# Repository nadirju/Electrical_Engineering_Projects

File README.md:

# Electrical_Engineering_Projects
This repository contains the projects I have done related to Electrical Engineering.

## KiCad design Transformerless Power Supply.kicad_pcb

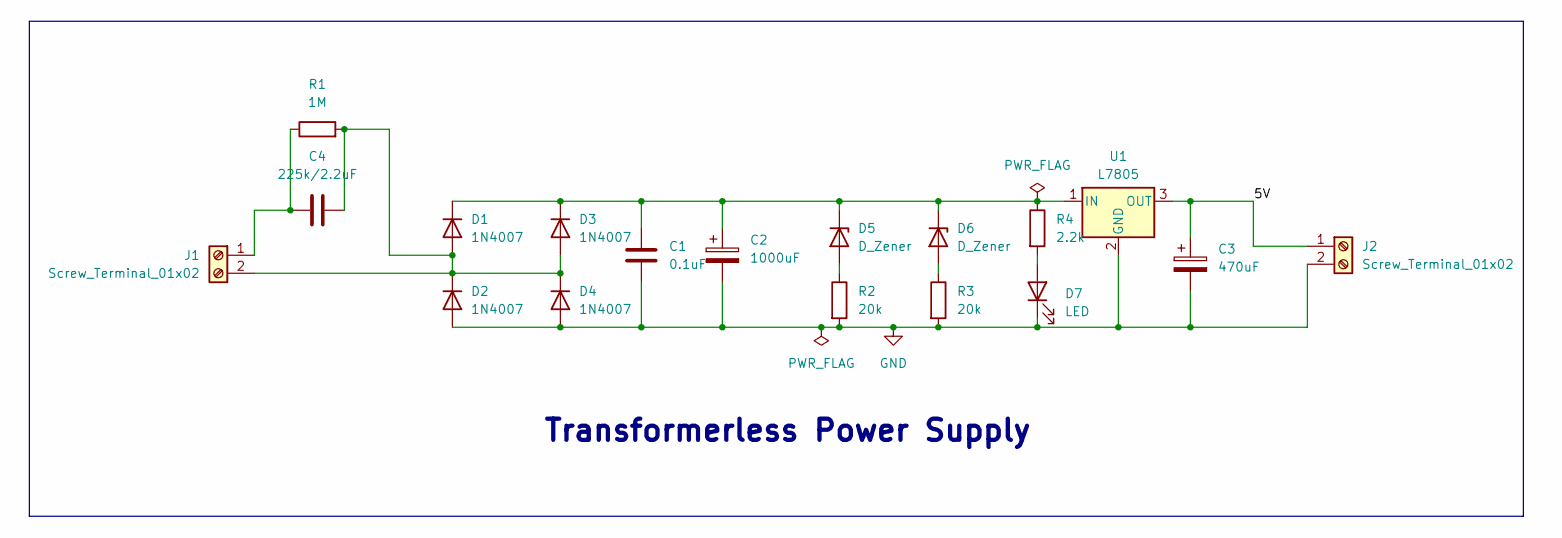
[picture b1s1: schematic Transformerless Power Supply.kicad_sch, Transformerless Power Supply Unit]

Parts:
C1: 0.1uF; C_Disc_D4.7mm_W2.5mm_P5.00mm
C2: 1000uF; CP_Radial_D10.0mm_P5.00mm
C3: 470uF; CP_Radial_D10.0mm_P3.80mm
C4: 225k/2.2uF; C_Rect_L18.0mm_W6.0mm_P15.00mm_FKS3_FKP3
D1, D2, D3, D4: 1N4007; D_DO-41_SOD81_P10.16mm_Horizontal
D5, D6: D_Zener; D_A-405_P7.62mm_Horizontal
D7: LED; LED_D5.0mm
J1, J2: Screw_Terminal_01x02; TerminalBlock_bornier-2_P5.08mm
R1: 1M; R_Axial_DIN0207_L6.3mm_D2.5mm_P7.62mm_Horizontal
R2, R3: 20k; R_Axial_DIN0207_L6.3mm_D2.5mm_P7.62mm_Horizontal
R4: 2.2k; R_Axial_DIN0207_L6.3mm_D2.5mm_P7.62mm_Horizontal
U1: L7805; TO-220-3_Vertical

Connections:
/5V: C3.1, J2.1, U1.3 (OUT)
GND: C1.2, C2.2, C3.2, D2.2 (A), D4.2 (A), D7.1 (K), J2.2, R2.2, R3.2, U1.2 (GND)
unnamed: C4.2, D1.2 (A), D2.1 (K), D3.2 (A), D4.1 (K), J1.2, R1.2
unnamed: C1.1, C2.1, D1.1 (K), D3.1 (K), D5.1 (K), D6.1 (K), R4.1, U1.1 (IN)
unnamed: D5.2 (A), R2.1
unnamed: D6.2 (A), R3.1
unnamed: D7.2 (A), R4.2
unnamed: C4.1, J1.1, R1.1

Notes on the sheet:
Transformerless Power Supply

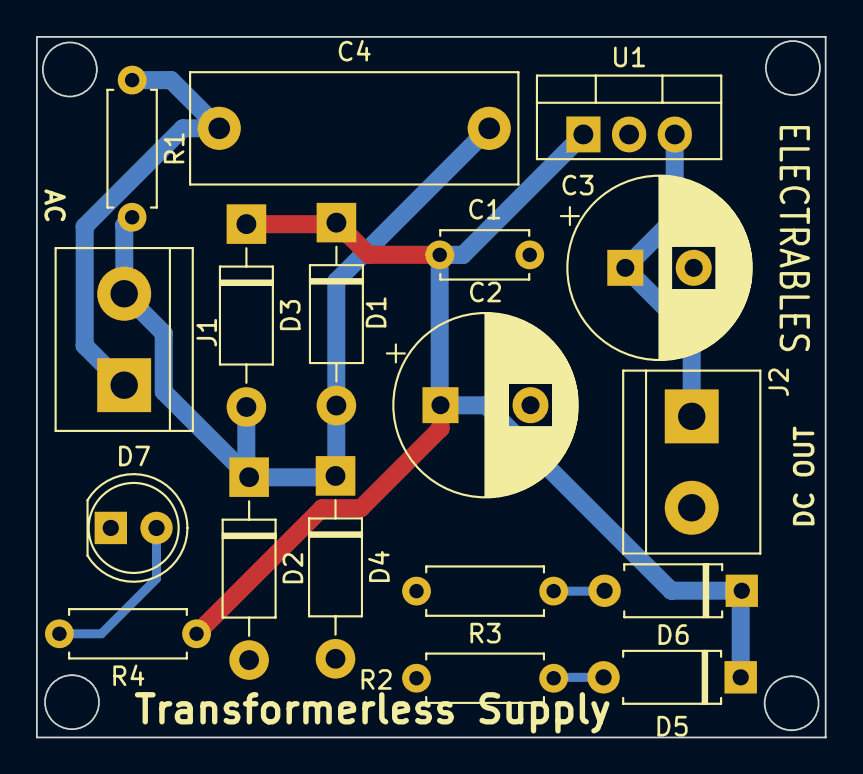
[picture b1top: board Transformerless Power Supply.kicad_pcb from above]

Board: 2 copper layers, 43.8 x 38.9 mm, 18 parts (0 on the bottom side), 8 nets.

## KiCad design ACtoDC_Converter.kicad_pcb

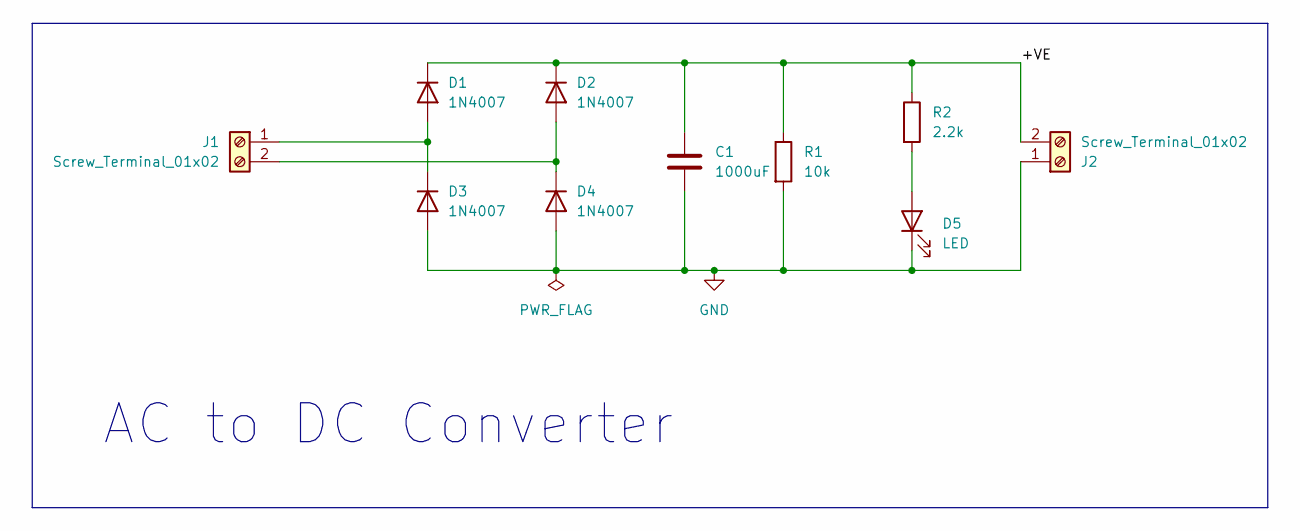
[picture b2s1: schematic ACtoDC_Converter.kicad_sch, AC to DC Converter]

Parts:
C1: 1000uF; C_Radial_D8.0mm_H11.5mm_P3.50mm
D1, D2, D3, D4: 1N4007; D_DO-41_SOD81_P10.16mm_Horizontal
D5: LED; LED_D5.0mm_Clear
J1, J2: Screw_Terminal_01x02; TerminalBlock_bornier-2_P5.08mm
R1: 10k; R_Axial_DIN0207_L6.3mm_D2.5mm_P7.62mm_Horizontal
R2: 2.2k; R_Axial_DIN0207_L6.3mm_D2.5mm_P7.62mm_Horizontal

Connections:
/+VE: C1.1, D1.1 (K), D2.1 (K), J2.2, R1.1, R2.1
GND: C1.2, D3.2 (A), D4.2 (A), D5.1 (K), J2.1, R1.2
unnamed: D1.2 (A), D3.1 (K), J1.1
unnamed: D2.2 (A), D4.1 (K), J1.2
unnamed: D5.2 (A), R2.2

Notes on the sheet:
AC to DC Converter

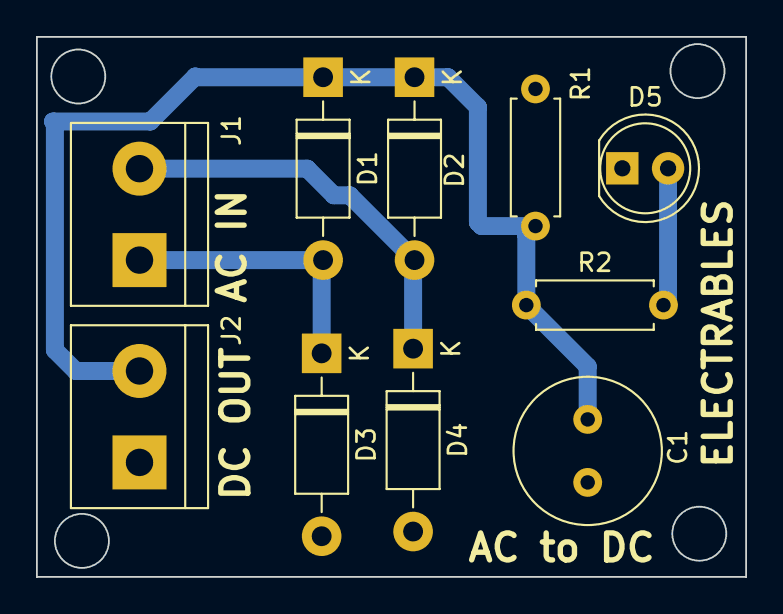
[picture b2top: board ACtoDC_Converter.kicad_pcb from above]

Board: 2 copper layers, 39.4 x 30.0 mm, 10 parts (0 on the bottom side), 5 nets.

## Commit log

2024-01-30 Add files via upload
    These are the files of LED Project which I have completed in Altium Designer recently.
2024-01-30 Revert "Add files via upload"
